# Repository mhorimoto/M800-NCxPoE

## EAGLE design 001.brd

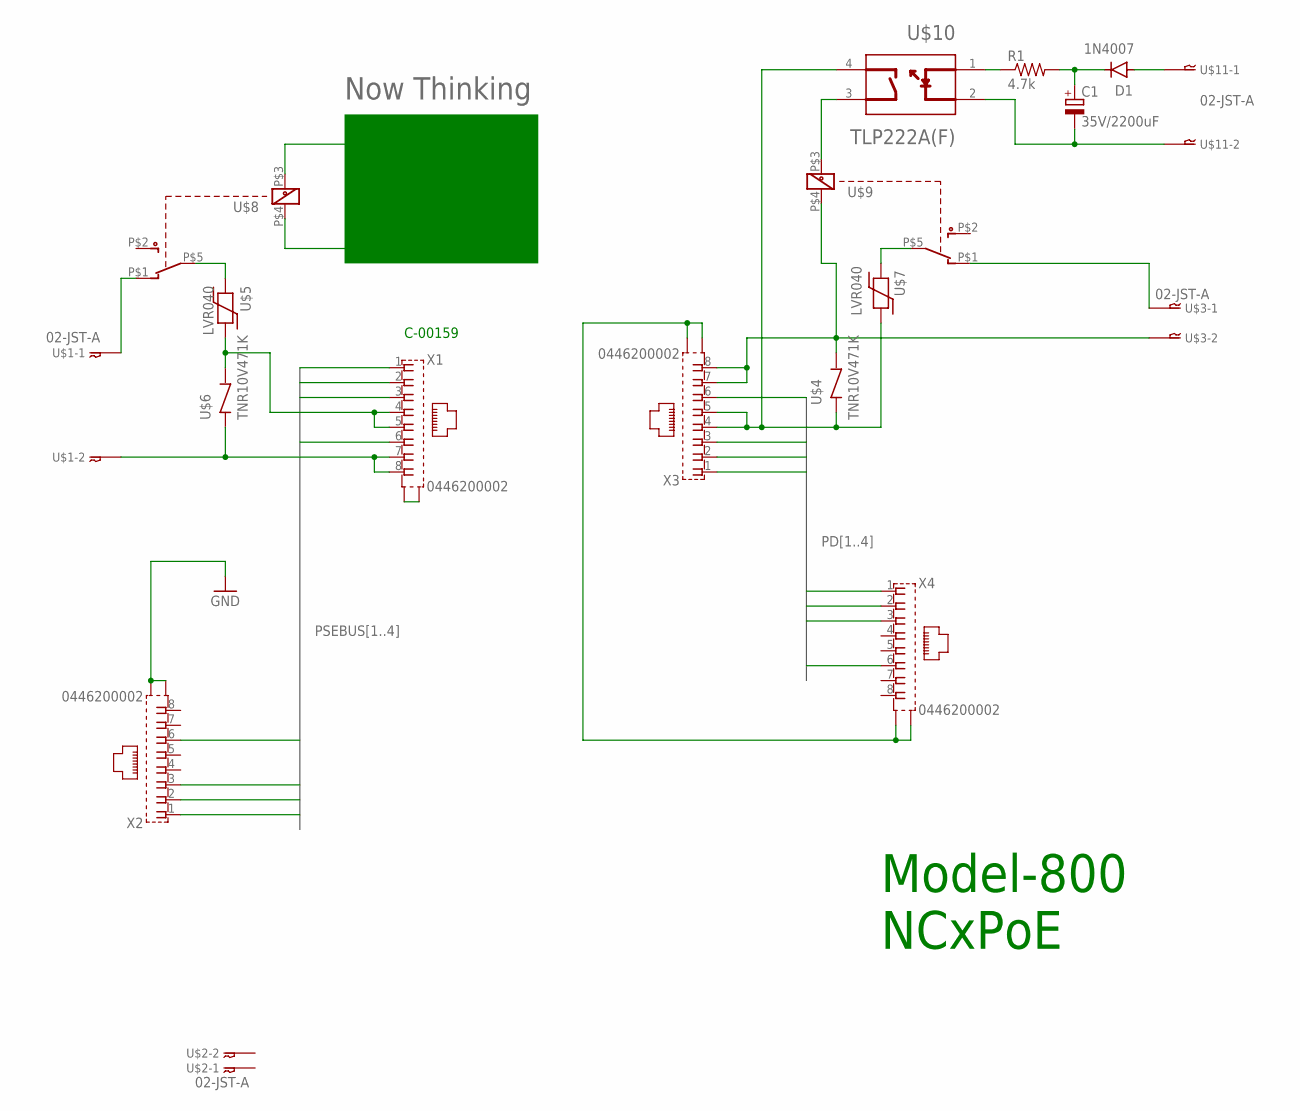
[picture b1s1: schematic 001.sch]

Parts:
C1: 35V/2200uF; E7,5-16
D1: 1N4007; DO-41
R1: 4.7k; 0207/5V
U$1, U$2, U$3, U$11: 02-JST-A; B02B-XH
U$4, U$6: TNR10V471K; 08-043X78_VARI
U$5, U$7: LVR040; 05-043X78
U$8, U$9: JQC-3FF
U$10: TOSHIBA_TLP222A_F_SIMPLE; TOSHIBA_TLP222A_F_0
X1, X2, X3, X4: 0446200002

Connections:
GND: X2.S@1 (S1), X2.S@2 (S2)
unnamed: U$5.2, U$8.P$5 (5)
unnamed: U$5.1, U$6.1, X1.4, X1.5
unnamed: U$1.P$2, U$6.2, X1.7, X1.8
unnamed: X1.S@1 (S1), X1.S@2 (S2)
unnamed: U$9.P$3 (1), U$10.3 (1_DRAIN)
unnamed: U$3.P$2, U$4.1, U$9.P$4 (2), X3.7, X3.8
unnamed: X3.S@1 (S1), X3.S@2 (S2), X4.S@1 (S1), X4.S@2 (S2)
unnamed: U$7.1, U$9.P$5 (5)
unnamed: U$1.P$1, U$8.P$1 (4)
unnamed: U$3.P$1, U$9.P$1 (4)
unnamed: U$8.P$3 (1), U$8.P$4 (2)
unnamed: R1.1, U$10.1 (ANODE)
unnamed: C1.+, D1.C, R1.2
unnamed: D1.A, U$11.P$1
unnamed: C1.-, U$10.2 (CATHODE), U$11.P$2
PD1: X3.1, X4.1
PD2: X3.2, X4.2
PD3: X3.3, X4.3
PD4: X3.6, X4.6
PSEBUS1: X1.1, X2.1
PSEBUS2: X1.2, X2.2
PSEBUS3: X1.3, X2.3
PSEBUS4: X1.6, X2.6
VCC_PD: U$4.2, U$7.2, U$10.4 (2_DRAIN), X3.4, X3.5

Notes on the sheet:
C-00159
Model-800 NCxPoE
Now Thinking

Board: 2 copper layers, 18 parts (0 on the bottom side), 25 nets, no tracks yet.

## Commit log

2020-06-22 リレーコイル電源を5V化する必要が有る場合にはレギュレータを入れる
2020-06-23 実機試験用
2020-06-28 これからPCB
2020-06-30 PSE側art work
2020-07-01 PCB変更とRJ45コネクタのFP作り
2020-07-02 もうちょっとRJ45コネクタは大変更
2020-07-03 RJ45 SOCKETを組み直し
2020-07-06 更に小型化
2020-07-18 一応完成、これからガーバー
2020-07-24 PSEとPDを別図面にした
2020-08-05 テストプログラム追加
2024-02-10 version合わせ
2024-12-23 KiCAD Version
